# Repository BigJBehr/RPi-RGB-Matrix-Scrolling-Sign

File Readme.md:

# Raspberry Pi RGB LED Matrix Scrolling Sign
This project is for a Raspberry Pi based RGB LED Matrix scrolling sign. A python script running on the Raspberry Pi uses WiFi and your internet connection to collect data from various web sites. The collected data is parsed, formatted and display on the RGB Matrix as scrolling text messages. The sign scrolls; time, date, quote-of-the-day, jokes, local weather, environment data, headlines, birthday greetings and holiday messages. The birthday and holiday greetings are user definable by editing a pair of XML files. Complete instructions on how to build one of these is available on the Instructables web site here; https://www.instructables.com/id/Raspberry-Pi-Scrolling-Sign/.

This is a list of the files found here. All of these files should be in the same directory on your Raspberry Pi.
    RGB-32x64.py    - python script that runs the scrolling display
    options.ini     - configuration file that is used to enable/disable features
    birthdays.xml   - file of birthday messages and dates
    holidays.xml    - file of holiday messages and dates
    samplebase.py   - python script from the Henner Zeller RGB matrix library
    fonts           - fonts directory from the Henner Zeller RGB matrix drive library
    Eagle           - this folder contains the Eagle files required to make your own boards

The Henner Zeller RGB matrix library should also be in this directory. You can get the library here; https://github.com/hzeller/rpi-rgb-led-matrix

## The Eagle folder has a zip file that has what is needed to send to a board manufacturer to make boards for you. It also has the Eagle schematic and board layout files and a PDF of the schematic.

Enjoy

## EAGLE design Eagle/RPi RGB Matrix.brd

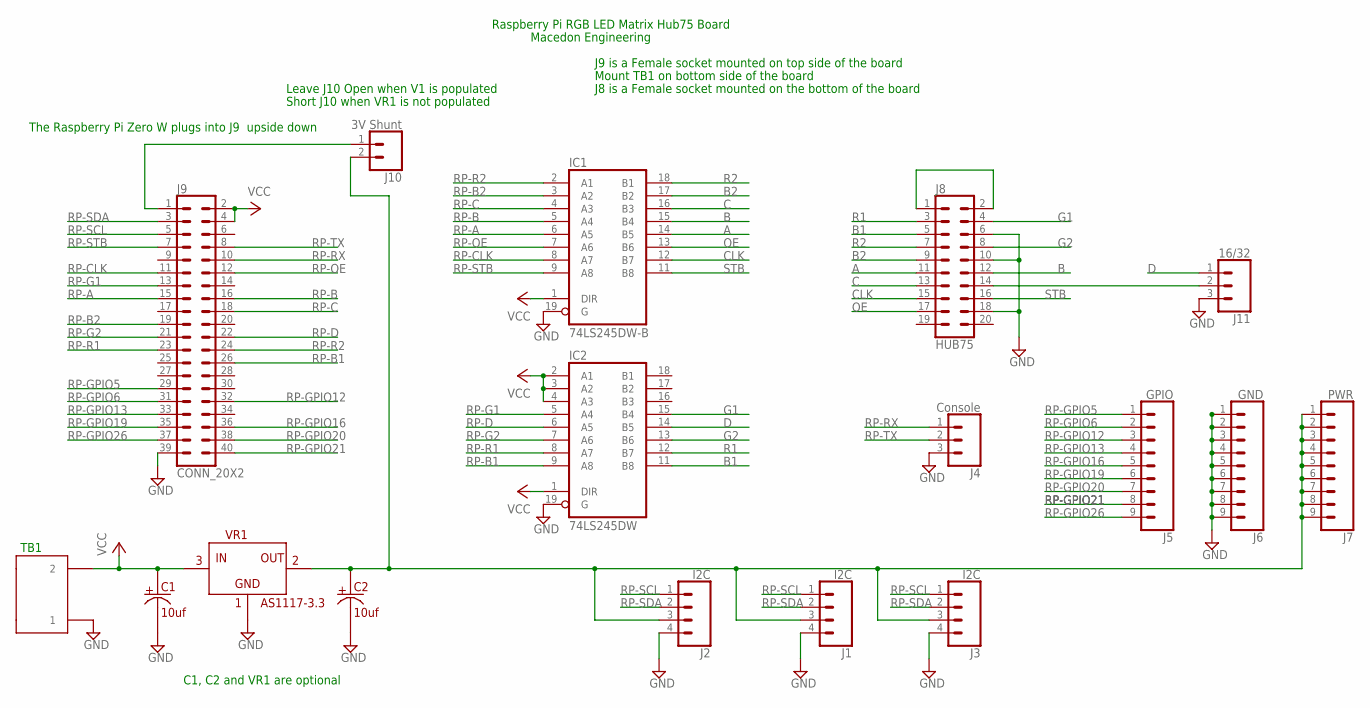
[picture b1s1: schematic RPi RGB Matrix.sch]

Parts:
C1, C2: 10uf; CAP-SMT-A
IC1: 74LS245DW-B; SO20W-B
IC2: 74LS245DW; SO20W
J1, J2, J3: I2C; 1X04
J4: Console; 1X03
J5: GPIO; 1X09
J6: GND; 1X09
J7: PWR; 1X09
J8: HUB75; 2X10
J9: CONN_20X2; 2X20
J10: 3V Shunt; 1X02
J11: 16/32; 1X03
TB1: TERMINALBLOCK-5MM-2POS
VR1: AS1117-3.3; SOT-223

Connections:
A: IC1.14 (B5), J8.11
B: IC1.15 (B4), J8.12
B1: IC2.11 (B8), J8.5
B2: IC1.17 (B2), J8.9
C: IC1.16 (B3), J8.13
CLK: IC1.12 (B7), J8.15
D: IC2.14 (B5), J11.1
G1: IC2.15 (B4), J8.4
G2: IC2.13 (B6), J8.8
GND: C1.P$2, C2.P$2, IC1.10 (GND), IC1.19 (G), IC2.10 (GND), IC2.19 (G), J1.4, J2.4, J3.4, J4.3, J6.1, J6.2, J6.3, J6.4, J6.5, J6.6, J6.7, J6.8, J6.9, J8.6, J8.10, J8.18, J9.39, J11.3, TB1.P$1 (1), TB1.P$4 (1), VR1.P$1
unnamed: J8.1, J8.2
unnamed: J9.1, J10.1
unnamed: C2.P$1, J1.3, J2.3, J3.3, J7.1, J7.2, J7.3, J7.4, J7.5, J7.6, J7.7, J7.8, J7.9, J10.2, VR1.P$2, VR1.P$4
unnamed: J8.14, J11.2
OE: IC1.13 (B6), J8.17
R1: IC2.12 (B7), J8.3
R2: IC1.18 (B1), J8.7
RP-A: IC1.6 (A5), J9.15
RP-B: IC1.5 (A4), J9.16
RP-B1: IC2.9 (A8), J9.26
RP-B2: IC1.3 (A2), J9.19
RP-C: IC1.4 (A3), J9.18
RP-CLK: IC1.8 (A7), J9.11
RP-D: IC2.6 (A5), J9.22
RP-G1: IC2.5 (A4), J9.13
RP-G2: IC2.7 (A6), J9.21
RP-GPIO5: J5.1, J9.29
RP-GPIO6: J5.2, J9.31
RP-GPIO12: J5.3, J9.32
RP-GPIO13: J5.4, J9.33
RP-GPIO16: J5.5, J9.36
RP-GPIO19: J5.6, J9.35
RP-GPIO20: J5.7, J9.38
RP-GPIO21: J5.8, J9.40
RP-GPIO26: J5.9, J9.37
RP-OE: IC1.7 (A6), J9.12
RP-R1: IC2.8 (A7), J9.23
RP-R2: IC1.2 (A1), J9.24
RP-RX: J4.1, J9.10
RP-SCL: J1.1, J2.1, J3.1, J9.5
RP-SDA: J1.2, J2.2, J3.2, J9.3
RP-STB: IC1.9 (A8), J9.7
RP-TX: J4.2, J9.8
STB: IC1.11 (B8), J8.16
VCC: C1.P$1, IC1.1 (DIR), IC1.20 (VCC), IC2.1 (DIR), IC2.2 (A1), IC2.3 (A2), IC2.4 (A3), IC2.20 (VCC), J9.2, J9.4, TB1.P$2 (2), TB1.P$3 (2), VR1.P$3

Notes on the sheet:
Raspberry Pi RGB LED Matrix Hub75 Board
Macedon Engineering
Mount TB1 on bottom side of the board
J9 is a Female socket mounted on top side of the board
J8 is a Female socket mounted on the bottom of the board
The Raspberry Pi Zero W plugs into J9 upside down
C1, C2 and VR1 are optional
Short J10 when VR1 is not populated
Leave J10 Open when V1 is populated
TB1

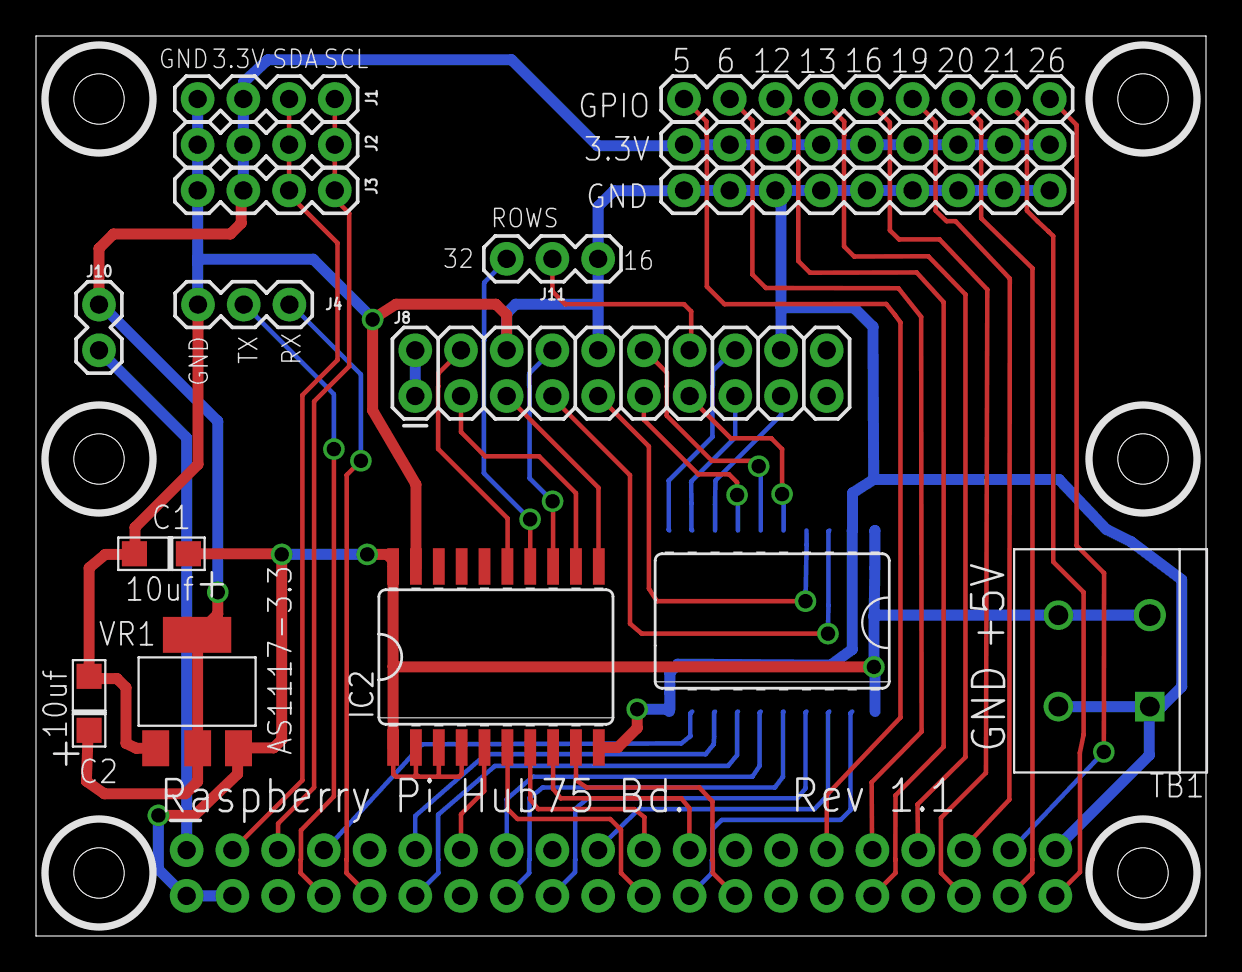
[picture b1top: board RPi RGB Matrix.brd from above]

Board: 2 copper layers, 65.0 x 50.0 mm, 17 parts (1 on the bottom side), 45 nets.

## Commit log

2018-01-04 Initial posting of all the files
    Initial posting of all the files
2018-01-04 Added link to Instructables site, added text about Eagle files
    Added link to Instructables site, added text about Eagle files
2018-04-28 changed military to true
    changed military to true
2018-04-28 changed back to military=f
    changed back to military=f
2018-04-28 test
    test to see if Crs are still being stripped
2018-04-28 test
    another test
2018-04-28 test
    yet another test
2018-04-28 Fixed issue with options.ini
    Fixed readOptions() to properly parsed files with carriage returns stripped out.
    Fixed timeMessage() to create time messages in military (24 hour) format.
    Renamed RGB-32x64 .py with RGB-32x64.py

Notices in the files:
parts and their libraries:
SparkFun-Connectors: Licensing: Creative Commons ShareAlike 4.0 International - https://creativecommons.org/licenses/by-sa/4.0
